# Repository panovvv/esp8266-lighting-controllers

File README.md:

# ESP8266 Lighting controllers

diyHue-compatible smart lighting controllers from inexpensive easy-to-source components.

* ESP-12 RGBCCT (5 channels) controller

    * Prototype
      
    * PCB render
      
    * PCB

    * Regular enclosure

    * Waterproof enclosure

* ESP-01 Neopixel (WS2812) controller

    * Schematic
      
    * Prototype

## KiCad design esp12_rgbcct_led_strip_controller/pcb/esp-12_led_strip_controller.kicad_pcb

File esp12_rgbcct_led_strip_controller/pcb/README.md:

# Files and folders:

* `esp-12_led_strip_controller.***, fp-lib-table` - KiCAD schematics and PCB files.
* `schematic.pdf` - full schematic sheet rendered in PDF.
* `bom.csv` - Bill of Materials, Tab-separated.
* `paper_footprint_test.pdf` - this is my usual practice when designing and ordering PCBs:
before even designing the board layout, I plot the empty board with all footprints in it to PDF
(1:1 scale), print it on a sheet of paper and do a "test fit" for every component. This helps 
to find footprint inconsistencies early on.
* `enclosure/` - OpenSCAD script + STL files. [Source](https://github.com/jbebel/Ultimate-Box-Maker)
* `enclosure_waterproof/` - waterproof enclosure (think bathrooms), designed in FreeCAD 0.18 . 
* `gerber/` - Generated according to
[this document](https://support.jlcpcb.com/article/102-kicad-515---generating-gerber-and-drill-files).
To order the PCB made, just zip up all files in `gerber/` folder and send to fab.
* `renders/` - 3D renders and STL of the board with all components populated.

# Dependencies

* _KF141V-6P_P2.54mm_ footprint from [Connector_KEFA_Homemade](https://github.com/panovvv/homemade-kicad-libraries) 

# BOM

| Designator          | Package                                                   | Quantity | Designation                                                                                    |
|---------------------|-----------------------------------------------------------|----------|------------------------------------------------------------------------------------------------|
| R1 - R7             | 0603 (1608 metric)                                        | 7        | 10k resistor.                                                                                  |
| U2                  | TO-220 3 pin                                              | 1        | LM1117-3.3 voltage regulator (3.3V)                                                            |
| C1, C4, C5          | 0603 (1608 metric)                                        | 3        | 100n capacitor.                                                                                |
| J3                  | KF141V-6P, 2.54mm spacing                                 | 1        | LED Strip connector – spring cage type.                                                        |
| C2                  | Radial polarized capacitor, D=10.0mm, P=5.00mm/7.50mm     | 1        | 1000u capacitor.                                                                               |
| C3                  | 0805 (2012 metric)                                        | 1        | 10u capacitor.                                                                                 |
| C6                  | EIA-6032-28 / Kemet-C, pad size: 2.25x2.35mm              | 1        | 100u tantalum capacitor (or any other capacitor that fits the footprint)                       |
| D1                  | DO-15                                                     | 1        | P6KE16A - TVS diode 16V.                                                                       |
| D2                  | SMA or SMB (Universal)                                    | 1        | Any surface mount diode in SMA or SMB package.                                                 |
| F1                  | Cylindric fuse holder - 5x20mm                            | 1        | LED strip fuse holder. Fuse current = total current consumption of your strip + some headroom. |
| F2                  | Disc capacitor, D=8.0mm, W=2.5mm, P=5.00mm                | 1        | PTC fuse, 0.5A.                                                                                |
| Q1, Q2, Q3, Q7, Q8  | TO-92                                                     | 5        | NPN transistor, EBC(123) configuration (e,g, 2N2222)                                           |
| Q4, Q5, Q6, Q9, Q10 | TO-220 3 pin.                                             | 5        | N type MOSFET, GDS(123) configuration (e,g, IRF3205)                                           |
| RN1, RN2            | Resistor array, convex, 4x0603                            | 2        | 10k resistor network.                                                                          |
| U1                  | ESP-12                                                    | 1        | ESP-12E or ESP-12F.                                                                            |
| J1                  | PhoenixContact MSTBVA 2,5 2-G-5,08, 1x02, 5.08mm spacing. | 1        | 12V input. Can be replaced with any similar connector.                                         |
| JP1                 | Pin header, 1x02, 2.54mm spacing.                         | 1        | PROG jumper.                                                                                   |
| J2                  | Pin header, 1x03, 2.54mm spacing.                         | 1        | UART male connector.                                                                           |
| J4                  | Pin socket, 1x02, 2.54mm spacing.                         | 1        | UART female connector.                                                                         |

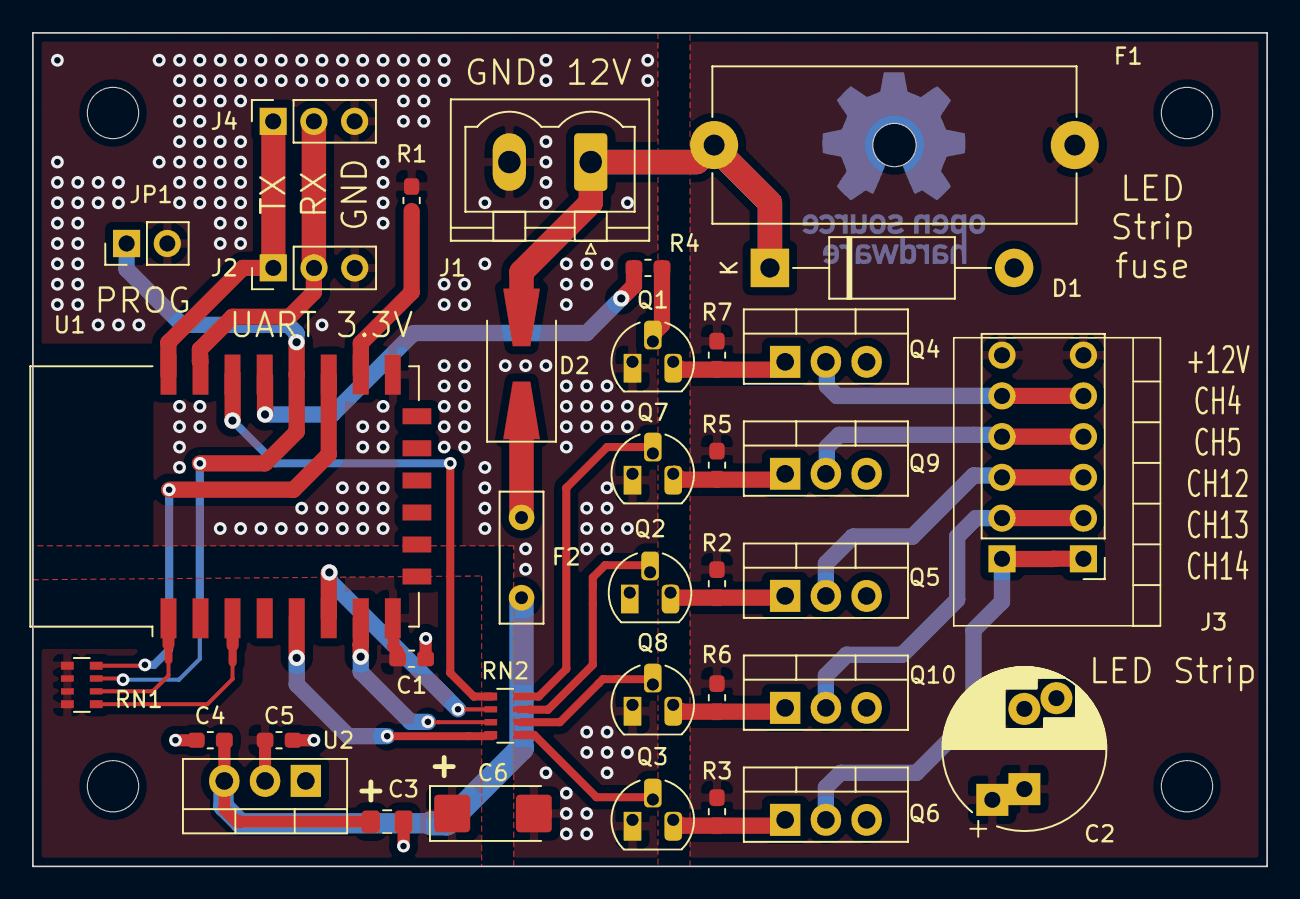
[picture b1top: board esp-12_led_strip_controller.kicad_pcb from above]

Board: 2 copper layers, 77.0 x 52.0 mm, 36 parts (0 on the bottom side), 33 nets.

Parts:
C1, C4, C5: 100n; C_0603_1608Metric_Pad1.05x0.95mm_HandSolder
C2: 1000u; CP_Radial_D10.0mm_P5.00mm_P7.50mm
C3: 10u; C_0805_2012Metric_Pad1.15x1.40mm_HandSolder
C6: 100u; CP_EIA-6032-28_Kemet-C_Pad2.25x2.35mm_HandSolder
D1: P6KE16A; D_DO-15_P15.24mm_Horizontal
D2: Any; D_SMA-SMB_Universal_Handsoldering
F1: LED Strip Fuse; Fuseholder_Cylinder-5x20mm_Schurter_0031_8201_Horizontal_Op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
F2: PTC 0.5A; C_Disc_D8.0mm_W2.5mm_P5.00mm
J1: 12V; PhoenixContact_MSTBVA_2,5_2-G-5,08_1x02_P5.08mm_Vertical
J2: UART_M; PinHeader_1x03_P2.54mm_Vertical
J3: LED Strip; KF141V-6P_P2.54mm
J4: UART_F; PinSocket_1x03_P2.54mm_Vertical
JP1: PROG jumper; PinHeader_1x02_P2.54mm_Vertical
Q1, Q2, Q3, Q7, Q8: NPN_EBC; TO-92_HandSolder
Q4, Q5, Q6, Q9, Q10: NMOSFET_GDS; TO-220-3_Vertical
R1, R2, R3, R4, R5, R6, R7: 10k; R_0603_1608Metric_Pad1.05x0.95mm_HandSolder
RN1, RN2: 10k; R_Array_Convex_4x0603
U1: ESP-12F; ESP-12E
U2: LM1117-3.3; TO-220-3_Vertical

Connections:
+3V3: C1.1, C5.1, C6.1, RN1.5, RN1.6, RN1.7, RN1.8, U1.8, U2.2
+12V: C2.1, F1.1, J3.6, R2.1, R3.1, R5.1, R6.1, R7.1
/CH4: J3.5, Q4.2
/CH5: J3.4, Q9.2
/CH12: J3.3, Q5.2
/CH13: J3.2, Q10.2
/CH14: J3.1, Q6.2
/UART_RX: J2.2, J4.2, U1.21
/UART_TX: J2.1, J4.1, U1.22
GND: C1.2, C2.2, C3.2, C4.2, C5.2, C6.2, D1.2, J1.2, J2.3, J4.3, JP1.2, Q1.1, Q2.1, Q3.1, Q4.3, Q5.3, Q6.3, Q7.1, Q8.1, Q9.3, Q10.3, R1.2, U1.15, U2.1
unnamed: C3.1, C4.1, F2.1, U2.3
unnamed: D1.1, D2.2, F1.2, J1.1
unnamed: D2.1, F2.2
unnamed: JP1.1, RN1.3, U1.18
unnamed: Q1.2, R4.1
unnamed: Q1.3, Q4.1, R7.2
unnamed: Q2.2, RN2.7
unnamed: Q2.3, Q5.1, R2.2
unnamed: Q3.2, RN2.5
unnamed: Q3.3, Q6.1, R3.2
unnamed: Q7.2, RN2.8
unnamed: Q7.3, Q9.1, R5.2
unnamed: Q8.2, RN2.6
unnamed: Q8.3, Q10.1, R6.2
unnamed: R1.1, U1.16
unnamed: R4.2, U1.19
unnamed: RN1.1, U1.3
unnamed: RN1.2, U1.1
unnamed: RN1.4, U1.17
unnamed: RN2.1, U1.20
unnamed: RN2.2, U1.6
unnamed: RN2.3, U1.7
unnamed: RN2.4, U1.5

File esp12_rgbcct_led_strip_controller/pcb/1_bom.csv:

2	Designator	Package	Quantity	Designation	Supplier and ref
3	R1 - R7	R_0603_1608Metric_Pad1.05x0.95mm_HandSolder	7	10k resistor	
4	U2	TO-220-3_Vertical	1	LM1117-3.3 voltage regulator	
5	C1, C4, C5	C_0603_1608Metric_Pad1.05x0.95mm_HandSolder	3	100n capacitor	
6	J3	KF141V-6P_P2.54mm	1	LED Strip connector – spring cage type.	
7	C2	CP_Radial_D10.0mm_P5.00mm_P7.50mm	1	1000u Polarized capacitor	
8	C3	C_0805_2012Metric_Pad1.15x1.40mm_HandSolder	1	10u capacitor (can be polarized)	
9	C6	CP_EIA-6032-28_Kemet-C_Pad2.25x2.35mm_HandSolder	1	100u capacitor	
10	D1	D_DO-15_P15.24mm_Horizontal	1	P6KE16A - TVS diode 16V	
11	D2	D_SMA-SMB_Universal_Handsoldering	1	Any surface mount diode	
12	F1	Fuseholder_Cylinder-5x20mm_Schurter_0031_8201_Horizontal_Open	1	LED Strip Fuse – pick current = total current consumption of your strip + some headroom	
13	F2	C_Disc_D8.0mm_W2.5mm_P5.00mm	1	PTC 0.5A	
14	Q1, Q2, Q3, Q7, Q8	TO-92_HandSolder	5	NPN_EBC	
15	Q4, Q5, Q6, Q9, Q10	TO-220-3_Vertical	5	N type MOSFET – GDS(123) pinout	
16	RN1, RN2	R_Array_Convex_4x0603	2	10k resistor network	
17	U1	ESP-12	1	ESP-12F	
18	J1	PhoenixContact_MSTBVA_2,5_2-G-5,08_1x02_P5.08mm_Vertical	1	12V input – any connector with 5.08mm. Spacing.	
19	JP1	PinHeader_1x02_P2.54mm_Vertical	1	PROG jumper	
20	J2	PinHeader_1x03_P2.54mm_Vertical	1	UART male connector	
21	J4	PinSocket_1x03_P2.54mm_Vertical	1	UART female connector

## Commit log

2020-03-27 Neopixel and RGBCCT controllers
    ESP01 neopixel controller + ESP12 RGBCCT LED strip controller, breadboard only for now
2020-03-29 base led strip controller for PCB
2020-04-20 esp-12 led strip controller PCB
2020-05-08 waterproof enclosure for ESP12 board
    more renders
2020-05-11 remove extra drill holes
2020-05-11 update readme.md
    include BOM
2020-05-12 update bom
    commit csv bom
2020-05-18 increase via size
2020-05-27 higher openscad box
2020-06-02 post-print update for RGBCCT c. box
2020-06-03 waterproof enclosure
    bigger SP16 holes
    switch to countersunk bolts
2021-03-28 minor fixes
2021-05-18 pictures in README.md
2021-08-28 more pictures in README.md
